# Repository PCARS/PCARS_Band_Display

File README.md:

# PCARS W4MLB Club Station Band Display

## Technical Project Summary

This project was developed for the Platinum Coast Amateur Radio Club (PCARS) to improve operational coordination at the W4MLB Club Station. It features a shared LED display that shows the active operating band and mode for two radio stations (Station 1 and Station 2), helping operators avoid frequency conflicts and manage dual-station operation more effectively.

---

## System Overview

The Band Display system consists of:

1. **ESP32-Based Control Unit**  
2. **Single Shared 64x64 RGB LED Matrix Display**  
3. **Audible Conflict Alert System**

<table>
  <tr>
    <td align="center">
      <br/>
      <sub>PCARS Band Display</sub>
    </td>
  </tr>
</table>

---

## Hardware Details

### Microcontroller
- **ESP32 DevKit V1**
  - Dual-core 32-bit microcontroller with Wi-Fi and Bluetooth
  - Interfaces with both radios via CI-V communication over UART
  - Processes band/mode data and drives the shared LED matrix display and alert system

### Display System
- **Single 64x64 RGB LED Matrix (HUB75 interface)**
  - Displays operating band and mode for both stations side-by-side
  - Color-coded segments for easy visual distinction between Station 1 and Station 2
  - Driven using the [ESP32-HUB75-MatrixPanel-I2S-DMA library](https://github.com/mrfaptastic/ESP32-HUB75-MatrixPanel-I2S-DMA) for high-performance, flicker-free display updates

### Radio Interface (Band/Mode Input)
- **CI-V Serial Bus Communication**
  - Each radio communicates band/mode data to the ESP32 via CI-V protocol
  - CI-V signals are connected to separate UART RX/TX pairs on the ESP32
  - Enables automated and accurate detection of each radio’s current state

### Power Supply
- **5V / 5A DC Input via 2.5mm Barrel Jack and Inline Mini Fuse Holder**
- **2-Position Screw Terminal for powering the LED matrix directly**, ensuring stable high-current delivery

### Alert System
- **Passive Buzzer (controlled via GPIO)**
  - Activates after 3 seconds if both stations are tuned to the same band
  - Logic controlled by the ESP32 to help operators avoid interference

### Connectors
- **2x8 Female Header (Bottom) + 2x8 Male Ribbon Header (Top)**
  - Used to interface the ESP32 Control Board to the LED matrix
  - Bottom connector allows direct plug-in to the matrix input (back-side mounting)
  - Top connector allows connection via standard ribbon cable

### PCB Design
- **2-layer Custom PCB**
  - Top layer features a +5V copper fill for power distribution
  - Bottom layer contains a solid ground pour with signal traces routed within
  - Compact and purpose-built layout for minimal noise and easy integration with the LED matrix

## Key Features
- Shared 64x64 LED matrix with real-time band/mode display for both stations  
- CI-V-based band/mode input over UART for accurate radio status monitoring  
- Conflict alert system buzzer with 3-second delay 
- ESP32-driven logic with efficient HUB75 display handling  
- Clean power distribution with dedicated matrix power input

## Software

The Band Display firmware is developed using the **Arduino framework** within **PlatformIO** on **Microsoft Visual Studio Code**. It leverages the multitasking capabilities of the ESP32 and includes purpose-built logic for real-time display updates, radio state monitoring, and conflict alerts.

### Key Components

- **PlatformIO Environment**  
  Ensures reproducible builds and dependency management.  
  Configuration is defined in `platformio.ini`.

- **ESP32-HUB75-MatrixPanel-I2S-DMA Library**  
  Handles high-speed updates to the 64x64 HUB75 RGB LED matrix.  
  This library utilizes the **ESP32's built-in DMA hardware** to stream pixel data directly to the matrix via the I2S peripheral.  
  Because the DMA engine manages the actual data transfer, the **main processor cores remain free** for other tasks such as serial parsing, logic processing, and display updates.  
  This results in **flicker-free, high-performance rendering** with minimal CPU overhead.  
  GitHub: [ESP32-HUB75-MatrixPanel-I2S-DMA](https://github.com/mrfaptastic/ESP32-HUB75-MatrixPanel-I2S-DMA)

- **CI-V Decoder Logic**  
  Parses incoming CI-V data from both radios over two **dedicated hardware UARTs** on the ESP32.  
  Using hardware UART peripherals ensures that incoming serial data is buffered and handled by the UART hardware itself—**without blocking or interrupting the main program flow**.  
  This allows for **reliable and real-time decoding** of Icom/Yaesu CI-V messages, even when both radios are transmitting data simultaneously.

- **Display Management**  
  Color-coded band/mode segments for each station.  
  Adaptive text sizing and positioning to fit the matrix resolution.  
  Designed to update dynamically based on the latest decoded band and mode data for each station.

- **Conflict Alert System**  
  When both stations are detected operating on the same band, a **passive buzzer** is used to annunciate the conflict.  
  The buzzer is driven using one of the **ESP32’s built-in PWM channels**, which allows tone generation **without burdening the processor with manual timing or waveform control**.  
  This hardware-driven approach ensures accurate and non-blocking sound output, keeping the main application responsive.

- **Task Scheduling**  
  Uses ESP32 FreeRTOS tasks for concurrent handling of:
  - CI-V communication  
  - Display updates  
  - Conflict alert logic  
  This structure allows each subsystem to operate independently without interfering with others, improving responsiveness and reliability.

  ---

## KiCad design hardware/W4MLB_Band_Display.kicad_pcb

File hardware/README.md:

This folder contains PCB design files for the PCARS Band Display interface/controller board.

This booard is designed to plug directly into the ribbon cable connector on the back side of a HUB75 LED Matrix.

It is small enough to fit inside the cavity behind the LED Matrix.

The board provide interfaces for CI-V buses from 2 different radios.

The board also has connections for a DC power supply to power the LED Matrix and ESP32 controller.

A passive buzzder is also included to allow for alerting when both radios are tuned to the same band.

The PCB was designed using the KiCAD design suite.

The Library folder contains sub-folders for the individual part's Symbols, Footprints and 3D models.

The parts library files were download primarily from the SnapEDA website.

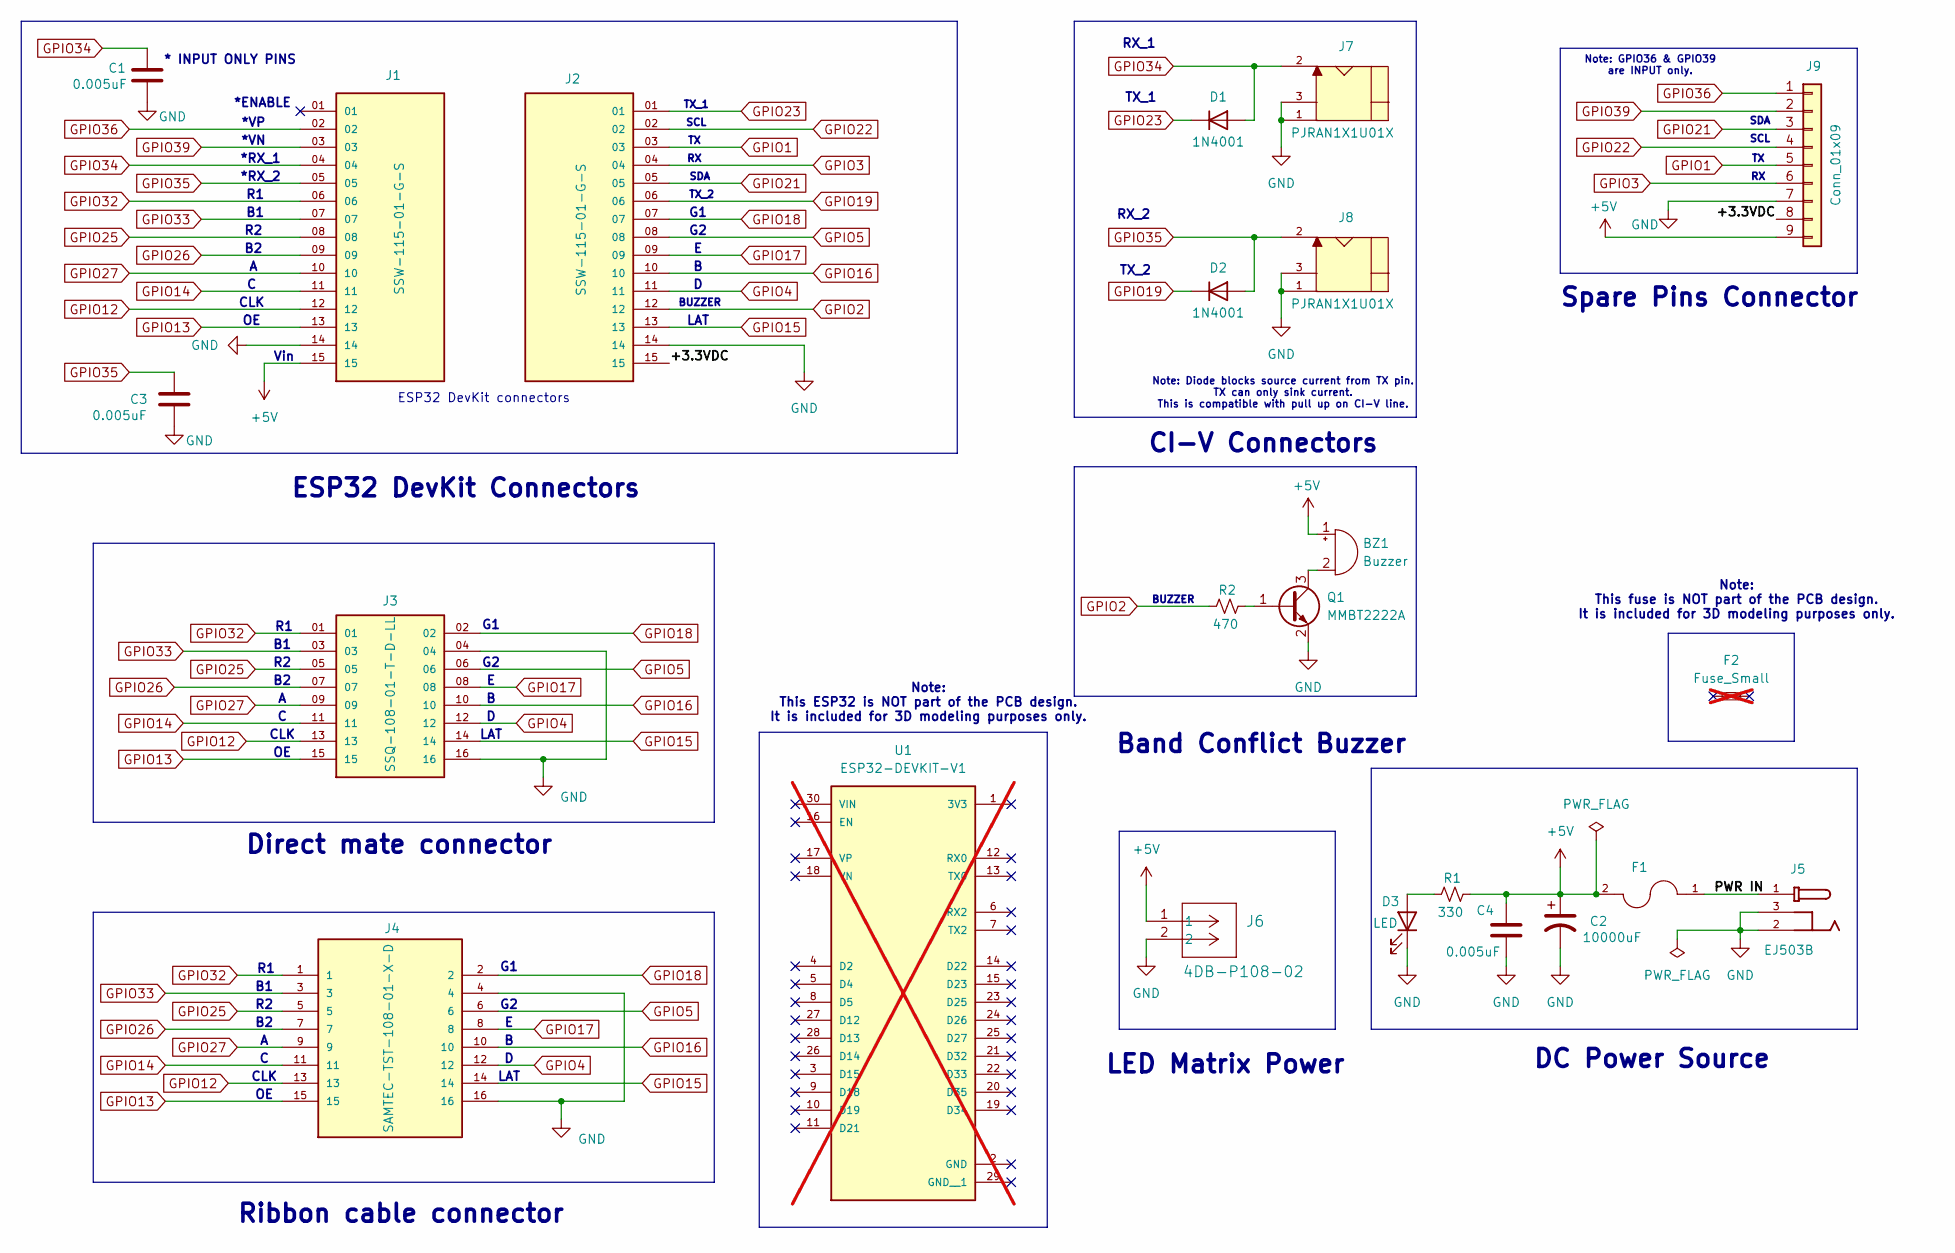
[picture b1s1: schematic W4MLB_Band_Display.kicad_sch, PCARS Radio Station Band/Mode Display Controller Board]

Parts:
BZ1: Buzzer; Buzzer_12x9.5RM7.6
C1, C3, C4: 0.005uF; C_0805_2012Metric_Pad1.18x1.45mm_HandSolder
C2: 10000uF; CP_Axial_L18.0mm_D8.0mm_P25.00mm_Horizontal
D1, D2: 1N4001; D_0805_2012Metric_Pad1.15x1.40mm_HandSolder
D3: LED; LED_0805_2012Metric_Pad1.15x1.40mm_HandSolder
F1: 3568-15; FUSE_3568-15; PARTREV C
F2: Fuse_Small; Fuse_Blade_Mini_directSolder; not fitted
J1, J2: SSW-115-01-G-S; SAMTEC_SSW-115-01-G-S; PARTREV R
J3: SSQ-108-01-T-D-LL; SAMTEC_SSQ-108-01-T-D-LL; PARTREV R
J4: SAMTEC-TST-108-01-X-D
J5: EJ503B; MPD_EJ503B; PARTREV B
J6: 4DB-P108-02; CONN_4DB-P108-02_TEC
J7, J8: PJRAN1X1U01X; SWITCHCRAFT_PJRAN1X1U01X; PARTREV A
J9: Conn_01x09; PinHeader_1x09_P2.54mm_Vertical
Q1: MMBT2222A; SOT-23
R1: 330; R_0805_2012Metric_Pad1.20x1.40mm_HandSolder
R2: 470; R_0805_2012Metric_Pad1.20x1.40mm_HandSolder
U1: ESP32-DEVKIT-V1; MODULE_ESP32_DEVKIT_V1; PARTREV N/A; not fitted

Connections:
+5V: BZ1.1 (+), C2.1, C4.1, F1.2, F1.4, J1.15, J6.1, J9.9, R1.2
/+3.3VDC: J2.15, J9.8
/PWR IN: F1.1, F1.3, J5.1
GND: C1.2, C2.2, C3.2, C4.2, D3.1 (K), J1.14, J2.14, J3.04, J3.16, J4.4, J4.16, J5.2, J5.3, J6.2, J7.1, J7.3, J8.1, J8.3, J9.7, Q1.2 (E)
GPIO1: J2.03, J9.5
GPIO2: J2.12, R2.1
GPIO3: J2.04, J9.6
GPIO4: J2.11, J3.12, J4.12
GPIO5: J2.08, J3.06, J4.6
GPIO12: J1.12, J3.13, J4.13
GPIO13: J1.13, J3.15, J4.15
GPIO14: J1.11, J3.11, J4.11
GPIO15: J2.13, J3.14, J4.14
GPIO16: J2.10, J3.10, J4.10
GPIO17: J2.09, J3.08, J4.8
GPIO18: J2.07, J3.02, J4.2
GPIO19: D2.1 (K), J2.06
GPIO21: J2.05, J9.3
GPIO22: J2.02, J9.4
GPIO23: D1.1 (K), J2.01
GPIO25: J1.08, J3.05, J4.5
GPIO26: J1.09, J3.07, J4.7
GPIO27: J1.10, J3.09, J4.9
GPIO32: J1.06, J3.01, J4.1
GPIO33: J1.07, J3.03, J4.3
GPIO34: C1.1, D1.2 (A), J1.04, J7.2
GPIO35: C3.1, D2.2 (A), J1.05, J8.2
GPIO36: J1.02, J9.1
GPIO39: J1.03, J9.2
unnamed: BZ1.2 (-), Q1.3 (C)
unnamed: D3.2 (A), R1.1
unnamed: Q1.1 (B), R2.2

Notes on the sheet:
Ribbon cable connector
SCL
TX_1
LED Matrix Power
DC Power Source
CLK
ESP32 DevKit connectors
*RX_2
TX_2
BUZZER
Note: Diode blocks source current from TX pin. TX can only sink current. This is compatible with pull up on CI-V line.
LAT
Note: This ESP32 is NOT part of the PCB design. It is included for 3D modeling purposes only.
Note: GPIO36 & GPIO39 are INPUT only.
RX_1
*VN
Band Conflict Buzzer
SDA
*ENABLE
ESP32 DevKit Connectors
* INPUT ONLY PINS
Vin
CI-V Connectors
Direct mate connector
RX_2
*RX_1
Note: This fuse is NOT part of the PCB design. It is included for 3D modeling purposes only.
Spare Pins Connector
*VP

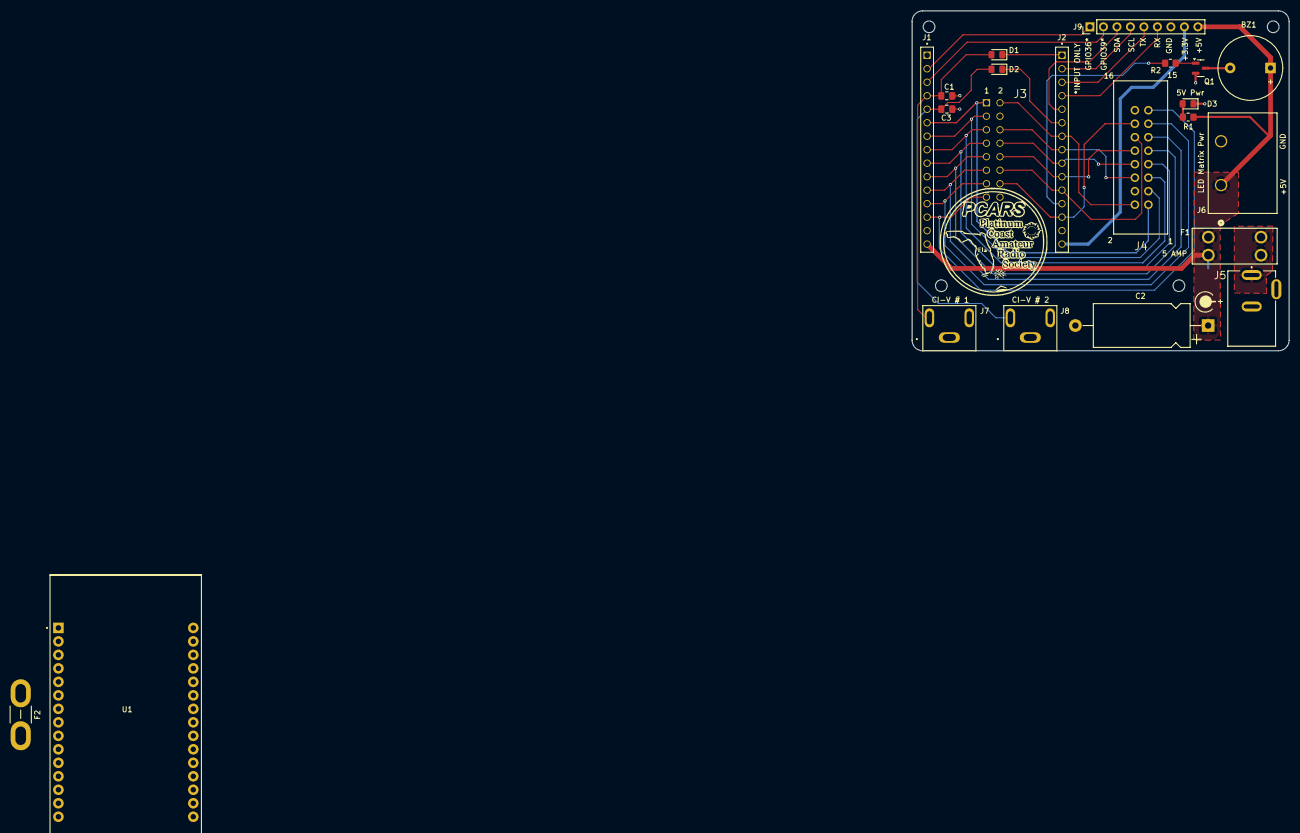
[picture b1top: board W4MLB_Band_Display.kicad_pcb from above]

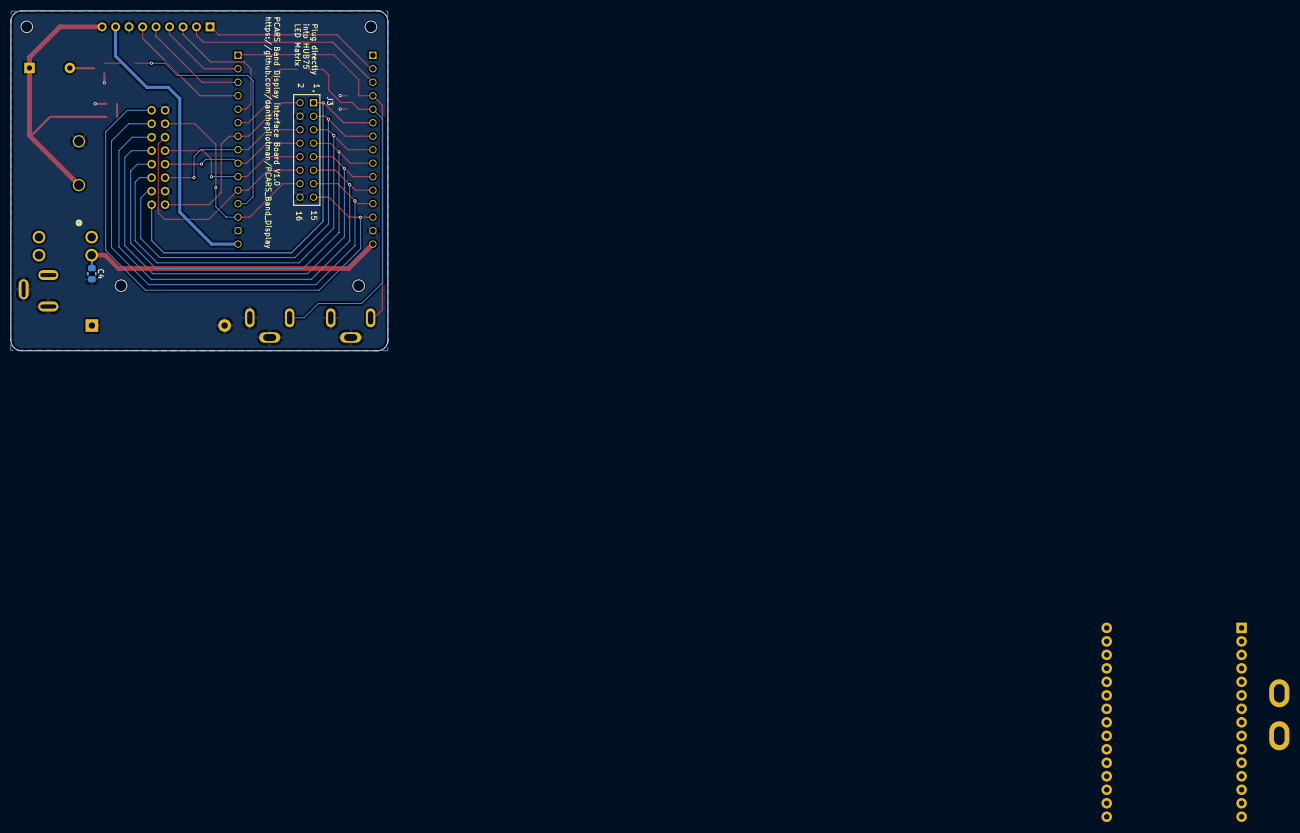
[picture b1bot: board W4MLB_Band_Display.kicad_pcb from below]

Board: 2 copper layers, 71.0 x 64.0 mm, 27 parts (2 on the bottom side), 32 nets.

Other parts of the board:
MH1, MH2, MH3, MH4: MountingHole_2.2mm_M2

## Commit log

2025-03-28 First commit. Basic CI-V receive capability. Also added LED Matrix display capability.
2025-03-30 Added display update functionality.
2025-03-31 Added extensive comments. Added reference documentation. Modified x,y positioning using #defines. Removed using station as a function argument since it is a global variable. Modified color codes to u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
2025-04-03 Moved pins around to reflect new connections on breadboard.
2025-04-09 Additional comments. Revised computeTextWidth function to use const char* vs String argument
2025-04-10 Reverted back to using Strings. Const char* was causing runtime crashes. Added query capability to initliaze display.
2025-04-10 Added #define for start of message (0xFE) Added #define for LED brightness Formatted spacing Added remaining print statements to utilize F( ) macro Modified query commands into a 2 dimensional array 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
2025-04-12 Initial Cpmmit
2025-04-14 First release candidate draft
    Laid out components and routed signals. Added silkscreen text and artwork
2025-04-17 Adjusted RX pins to input only pins to save GPIO. Removed placeholder text for Amp power, antenna and RX/TX. Added band conflict checker.
2025-04-17 Removed printing of redundant units for band
2025-04-17 Buzzer
    Added buzzer. Rearranged pins to make use of INPUT only pins for RX. Also reallocated different pins to the spare pins header and placed it in a better location.
2025-04-17 Updated platform to 6.10.0 latest version. Modified platform to DevKit -V1 instead of generic. Removed #define for LED_BUILTIN, Removed "New" from print "New Band". Renamed ledOn to led_On. Added a f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
2025-04-18 Finisghing touches
    Added fillets and chamfers to Cu zones. Adjusted silkscreen text and graphics.
    Added mounting holes.
2025-04-18 Move PlatformIO files to firmware/
2025-04-18 Move KiCad files to hardware/
2025-04-18 Added firmware
2025-04-18 Update firmware gitignore
2025-04-18 Minor changes to json and gitignore files
2025-04-18 Add /hardware gitignore file
2025-04-18 Untrack W4MLB_Band_Display-backups folder
2025-04-18 Deleted redundant /firmware folder inside /hardware folder.
2025-04-18 Update README.md
    Added details and 3D model images.
2025-04-18 Update README.md
    Added board bottom view.
2025-04-18 Added 3D model images.
2025-04-18 Added code to drive passive buzzer for band conflict alerts.
2025-04-18 Screw terminal connector & Datasheets
    Replaced LED Matric power connector with 2 position screw terminal for spade terminals. Also added datasheets for connector parts.
2025-04-19 Added LibreCAD drawing
    CAD drawing shows vertical stack up of parts. Also shows clearance from top and bottom side of PCB to LED Matrix cavity.
2025-04-19 Created Mech CAD folder.
    Moved dxf CAD design files to new folder. Created PDF for easy viewing.
2025-04-19 Removed rogue file
2025-04-19 Clean up of dxf files
2025-04-20 Moved Ref Docs & Corrected Buzzer pin
    Moved Reference docs from /firmware/libs to Reference Docs at upper level.
    Fixed issue where GPIO19 was connected to both TX and Buzzer. Moved buzzer to GPIO2
2025-04-20 Cleaned up code for buzzer activation. Removed LED_BUILTIN digital pin code.
2025-04-20 Changed 10 pin connector to 9 pin
    Modified 10 pin connector to 9 pins after assignment of GPIO2 to buzzer and it no longer being a spare pin.
2025-04-22 Smaller terminal block
    Changed terminal block to smaller footprint.
    Moved PCARS logo to front silkscreen.
    Added RF bypass caps to CI-V inputs.
    Adjusted location of D1 & D2.
    Modified F1 footprint to allow pins 3 &4 to be connected.
2025-04-22 Updated Mechanical Stack Up CAD Drawings
    Updated Mechanical Stack Up CAD Drawings to reflect change in terminal block connector dimensions.
2025-04-22 Added RF bypass cap to +5V DC supply input.
2025-04-23 Added V2.0
    Added V2.0 which connects LED Matrix power via an onboard connector on the bottom of the board.
2025-04-24 Fixed bug in code that prevented buzzer from triggering
    Fixed code to allow for buzzer to activate.
    Moved station #s down to second row.
2025-04-24 Adjustment to parts locations
2025-04-24 Added two tone siren option
2025-04-30 Updates to V1 & V2 boards
    Updated location of +5V LED Matric power connector on V2 board after careful measurements.
    Made final changes to V1 board before sending off to fabrication.
2025-04-30 Consolidated drill file into Gerber folder
    Recompiled drill file into a single file and placed it inside the Gerber folder instead of it's own Drill folder.
2025-05-12 Updated firmware to handle when radios are off. Band conflict check now queries both radios to make sure they are on before triggering alarm.
    Also updated V1 of PCB with latest gerber files.
2025-05-14 Added and cleaned up comments. Swapped order of execution on band conflict and display update in loop function. Added code to clear displayed band and mode data if radio goes unresponsive to queries.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
2025-05-14 Updated images to reflect actual V1 build
2025-05-14 Updated links to board 3D image files
2025-05-14 Removed links to 3D board images
2025-05-14 Updated V2 board 3D images
2025-05-14 Updated 3D board images
2025-05-14 Added HTML BOM to README for V1
2025-05-14 Change HTML BOM to a link
2025-05-14 Updated HTML BOM link text
2025-05-14 Added bold section text header for BOM link
2025-05-14 Swapped location of images and BOM
2025-05-14 Moved query_radio function prototype declaration from setup.h to CI-V.h
2025-05-14 Added Software details to the readme file
2025-05-16 V1 board correction for large radial capacitor. D10mm x L20mm
    Previous 3D mode for large bulk capacitor was incorrect. Updated to right size D10mm x L20mm
2025-05-17 1. Modified logic for band detection to avoid repeated queries to the radios unless the bands are in conflict. 2. Added quiet bus checks before transmitting query commands.
2025-05-17 Updated code to work with radio queries exclusively.
    Changed how code communicates with radios. Instead of passively listening for CI-V packets, the ESP will now query the radios periodically. This allows for cases where one radio comes online at a lat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
